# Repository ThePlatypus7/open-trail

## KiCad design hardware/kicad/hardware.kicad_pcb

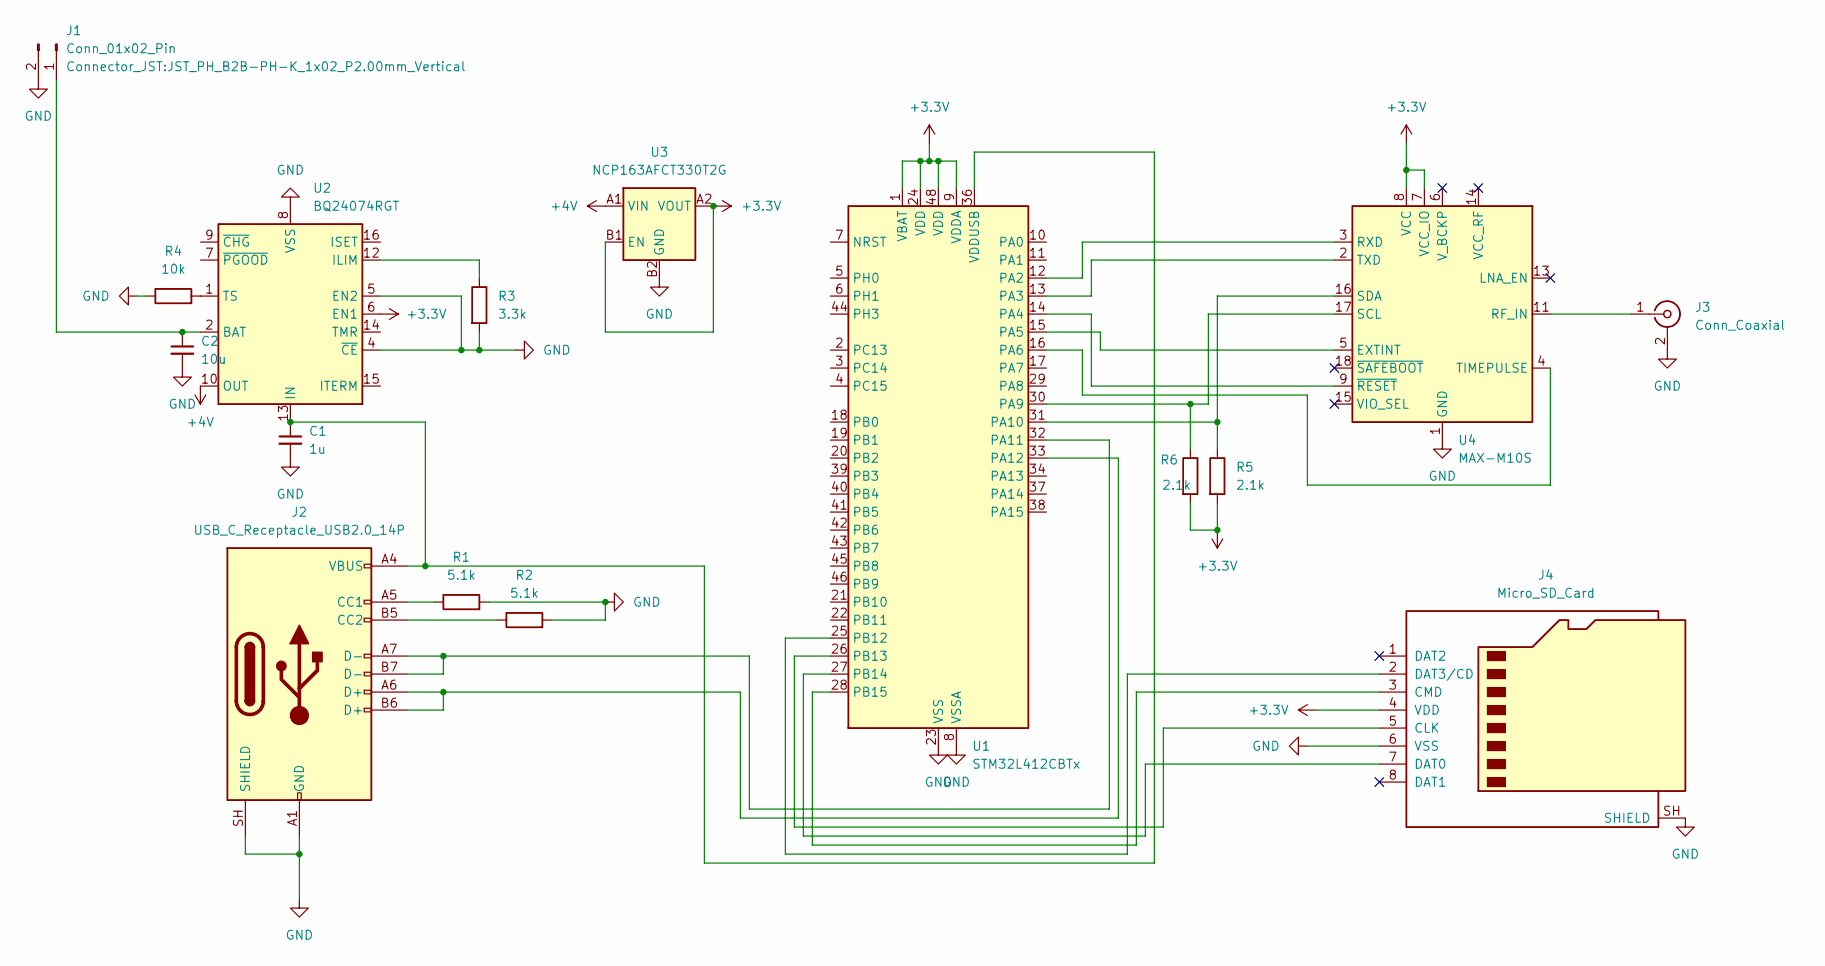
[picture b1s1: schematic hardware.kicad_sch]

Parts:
C1: 1u; C_0805_2012Metric
C2: 10u; C_0805_2012Metric
J1: Conn_01x02_Pin; JST_PH_B2B-PH-K_1x02_P2.00mm_Vertical
J2: USB_C_Receptacle_USB2.0_14P; USB_C_Receptacle_HRO_TYPE-C-31-M-12
J3: Conn_Coaxial; U.FL_Hirose_U.FL-R-SMT-1_Vertical
J4: Micro_SD_Card; microSD_HC_Hirose_DM3AT-SF-PEJM5
R1, R2: 5.1k; R_0805_2012Metric
R3: 3.3k; R_0805_2012Metric
R4: 10k; R_0805_2012Metric
R5, R6: 2.1k; R_0805_2012Metric_Pad1.20x1.40mm_HandSolder
U1: STM32L412CBTx; LQFP-48_7x7mm_P0.5mm
U2: BQ24074RGT; VQFN-16-1EP_3x3mm_P0.5mm_EP1.6x1.6mm
U3: NCP163AFCT330T2G; WLCSP-4_0.64x0.64mm_Layout2x2_P0.35mm
U4: MAX-M10S; ublox_MAX

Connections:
+3.3V: J4.4 (VDD), R5.2, R6.2, U1.1 (VBAT), U1.9 (VDDA), U1.24 (VDD), U1.48 (VDD), U2.6 (EN1), U3.A2 (VOUT), U3.B1 (EN), U4.7 (VCC_IO), U4.8 (VCC)
+4V: U2.10 (OUT), U2.11 (OUT), U3.A1 (VIN)
GND: C1.2, C2.2, J1.2, J2.A1 (GND), J2.A12 (GND), J2.B1 (GND), J2.B12 (GND), J2.SH (SHIELD), J3.2 (Ext), J4.6 (VSS), J4.SH (SHIELD), R1.2, R2.2, R3.2, R4.1, U1.8 (VSSA), U1.23 (VSS), U1.35 (VSS), U1.47 (VSS), U2.4 (~CE), U2.5 (EN2), U2.8 (VSS), U2.17 (VSS), U3.B2 (GND), U4.1 (GND), U4.10 (GND), U4.12 (GND)
unnamed: C2.1, J1.1, U2.2 (BAT), U2.3 (BAT)
unnamed: J2.A5 (CC1), R1.1
unnamed: J2.B5 (CC2), R2.1
unnamed: J3.1 (In), U4.11 (RF_IN)
unnamed: J4.5 (CLK), U1.26 (PB13)
unnamed: J4.3 (CMD), U1.28 (PB15)
unnamed: J4.7 (DAT0), U1.27 (PB14)
unnamed: J4.2 (DAT3/CD), U1.25 (PB12)
unnamed: U1.12 (PA2), U4.3 (RXD)
unnamed: U1.13 (PA3), U4.2 (TXD)
unnamed: U1.14 (PA4), U4.9 (~RESET)
unnamed: U1.15 (PA5), U4.5 (EXTINT)
unnamed: U1.16 (PA6), U4.4 (TIMEPULSE)
unnamed: R6.1, U1.30 (PA9), U4.17 (SCL)
unnamed: R5.1, U1.31 (PA10), U4.16 (SDA)
unnamed: J2.A7 (D-), J2.B7 (D-), U1.32 (PA11)
unnamed: J2.A6 (D+), J2.B6 (D+), U1.33 (PA12)
unnamed: C1.1, J2.A4 (VBUS), J2.A9 (VBUS), J2.B4 (VBUS), J2.B9 (VBUS), U1.36 (VDDUSB), U2.13 (IN)
unnamed: R3.1, U2.12 (ILIM)
unnamed: R4.2, U2.1 (TS)

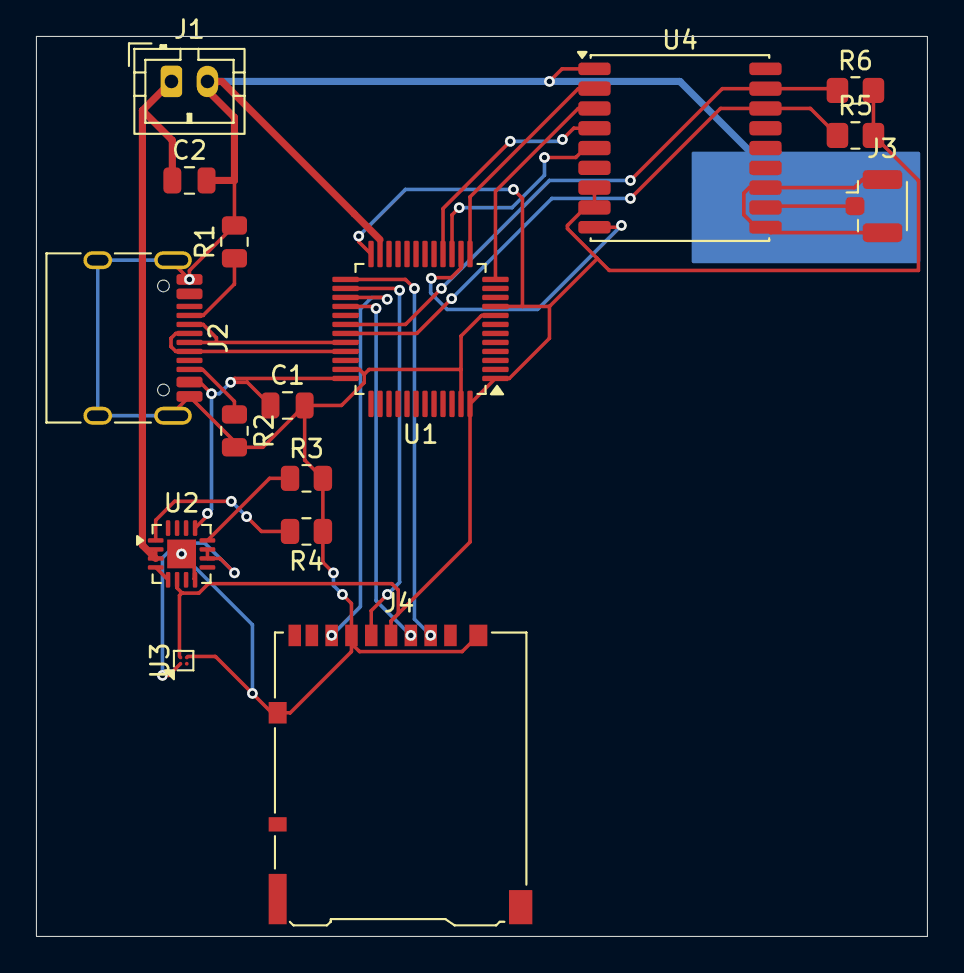
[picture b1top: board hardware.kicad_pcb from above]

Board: 2 copper layers, 49.5 x 50.0 mm, 16 parts (0 on the bottom side), 23 nets.

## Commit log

2026-05-19 initial
2026-05-19 add license
2026-05-19 added kicad and restructure project
2026-05-19 Create LICENSE
2026-05-19 power management
2026-05-19 connect gps receiver and add sd card slot
2026-05-19 reroute main pcb
